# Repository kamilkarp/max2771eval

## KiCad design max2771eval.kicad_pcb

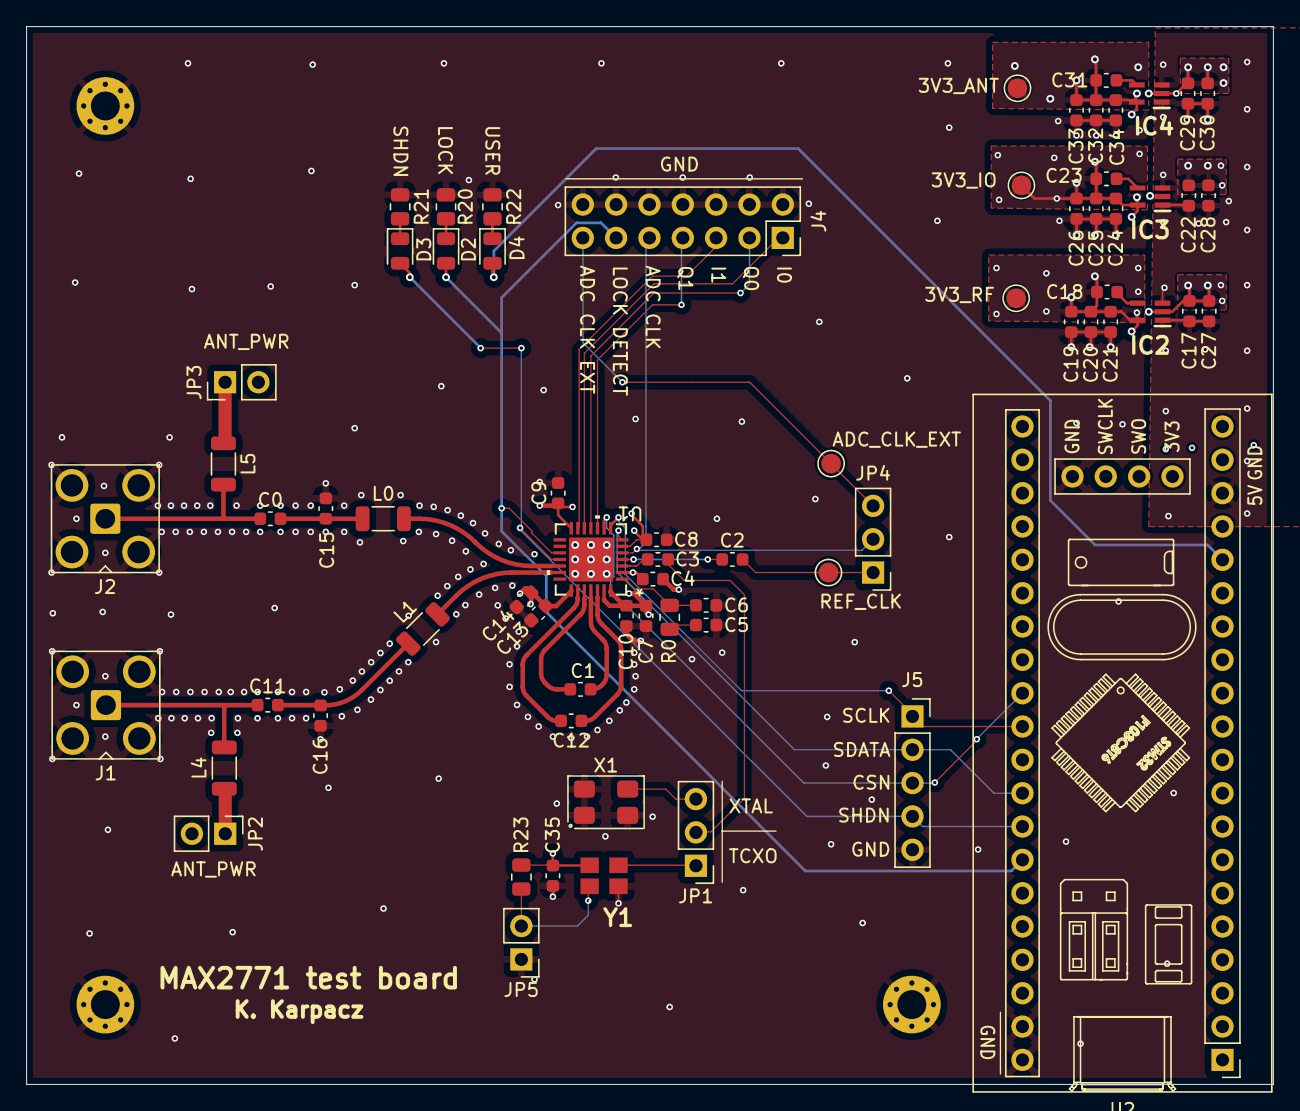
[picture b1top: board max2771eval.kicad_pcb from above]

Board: 4 copper layers, 95.0 x 80.6 mm, 72 parts (0 on the bottom side), 44 nets.

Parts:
C0, C1, C11, C12: 0.47nF; C_0603_1608Metric
C2, C3, C18, C20, C23, C25, C31, C33, C35: 10nF; C_0603_1608Metric
C4, C7, C8, C9, C10, C13, C17, C19, C22, C24, C30, C32: 0.1μF; C_0603_1608Metric
C5: 0.75nF; C_0603_1608Metric
C6: 15pF; C_0603_1608Metric
C14: 0.1nF; C_0603_1608Metric
C15: 1.7 pF; C_0603_1608Metric
C16: 1.1 pF; C_0603_1608Metric
C21, C26, C27, C28, C29, C34: 1μF; C_0603_1608Metric
D2, D3, D4: LED; D_0805_2012Metric
H1, H2, H3: MountingHole_Pad; MountingHole_2.2mm_M2_Pad_Via
IC2, IC3, IC4: MAX8510EXK33+T; SOT65P210X110-5N
J1, J2: Conn_Coaxial; SMA_Amphenol_901-143_Horizontal
J4: Conn_02x07_Odd_Even; PinSocket_2x07_P2.54mm_Vertical
J5: Conn_01x05_Socket; PinSocket_1x05_P2.54mm_Vertical
JP1, JP4: Jumper_3_Bridged12; PinHeader_1x03_P2.54mm_Vertical
JP2, JP3: Jumper_2_Bridged; PinHeader_1x02_P2.54mm_Vertical
JP5: Jumper_2_Open; PinHeader_1x02_P2.54mm_Vertical
L0: 5.6 nH; L_1206_3216Metric
L1: 8.4 nH; L_1206_3216Metric
L4, L5: 5.6nH; L_1206_3216Metric
R0: 15k; R_0805_2012Metric
R20, R21, R22: 1k; R_0805_2012Metric
R23: 25k; R_0805_2012Metric
TP1: 3V3_ANT; TestPoint_Pad_D1.5mm
TP2: 3V3_RF; TestPoint_Pad_D1.5mm
TP3: 3V3_IO; TestPoint_Pad_D1.5mm
TP4: ADC_CLK_EXT; TestPoint_Pad_D1.5mm
TP5: REF_CLK; TestPoint_Pad_D1.5mm
U1: MAX2771ETI+; 21-0140L_T2855-8_MXM
U2: YAAJ_BluePill_SWD_Breakout; YAAJ_BluePill_SWD_1
X1: 16.368MHz; Crystal_SMD_5032-4Pin_5.0x3.2mm
Y1: ATX-H11-F-24.000MHz-F25-T; ATXH11F24000MHzF25T

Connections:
+3.3V_IO: C8.1, C9.1, C23.2, C24.1, C25.1, C26.1, C35.2, IC3.5 (OUT), R23.2, TP3.1, U1.6 (VCCD), U1.14 (VCCADC), Y1.4 (VDD)
+3.3V_RF: C4.1, C7.1, C10.2, C13.2, C14.2, C18.2, C19.1, C20.1, C21.1, IC2.5 (OUT), TP2.1, U1.2 (VCCCP), U1.22 (VCCRF), U1.27 (VCCIF), U1.28 (VCCVCO)
+3.3_ANT: C31.2, C32.1, C33.1, C34.1, IC4.5 (OUT), JP2.2 (B), JP3.2 (B), TP1.1
+5V_USB: C17.2, C22.2, C27.1, C28.1, C29.1, C30.2, IC2.1 (IN), IC2.3 (~SHDN), IC3.1 (IN), IC3.3 (~SHDN), IC4.1 (IN), IC4.3 (~SHDN), U2.18 (5V)
/ADC_CLK_A: J4.9, JP4.2 (C), U1.5 (ADC_CLKIN)
/ADC_CLK_A_EXT: J4.13, JP4.3 (B), TP4.1
/A_CSN: J5.3, U1.9 (CSN), U2.29 (PA4)
/A_I0: J4.1, U1.12 (I0)
/A_I1: J4.5, U1.13 (I1)
/A_LOCK_DETECT: D2.2 (A), J4.11, U1.17 (LD), U2.34 (PB1)
/A_Q0: J4.3, U1.11 (Q0)
/A_Q1: J4.7, U1.10 (Q1)
/A_SCLK: J5.1, U1.8 (SCLK), U2.30 (PA5)
/A_SDATA: J5.2, U1.7 (SDATA), U2.32 (PA7)
/A_SHDN: D3.2 (A), J5.4, U1.18 (SHDN), U2.33 (PB0)
/REF_CLK_A: C3.2, JP1.2 (C)
/REF_CLK_OUT_A: C2.2, JP4.1 (A), TP5.1
/RF_HIGH_BAND_IN_A: C0.1, J2.1 (In), L5.2
/RF_LOW_BAND_IN_A: C11.1, J1.1 (In), L4.2
GND: C4.2, C5.2, C6.2, C7.2, C8.2, C9.2, C10.1, C13.1, C14.1, C15.1, C16.1, C17.1, C19.2, C20.2, C21.2, C22.1, C24.2, C25.2, C26.2, C27.2, C28.2, C29.2, C30.1, C32.2, C33.2, C34.2, C35.1, H1.1, H2.1, H3.1, IC2.2 (GND), IC3.2 (GND), IC4.2 (GND), J1.2 (Ext), J2.2 (Ext), J4.2, J4.4, J4.6, J4.8, J4.10, J4.12, J4.14, J5.5, JP5.1 (A), R20.1, R21.1, R22.1, U1.29 (EPAD), U2.19 (GND), U2.39 (GND), U2.40 (GND), U2.41 (GND), X1.1, X1.2, X1.4, Y1.2 (GND)
unnamed: C0.2, C15.2, L0.1
unnamed: C5.1, R0.1
unnamed: C11.2, C16.2, L1.1
unnamed: D2.1 (K), R20.2
unnamed: D3.1 (K), R21.2
unnamed: D4.2 (A), U2.16 (PB8)
unnamed: D4.1 (K), R22.2
unnamed: C18.1, IC2.4 (BP)
unnamed: C23.1, IC3.4 (BP)
unnamed: C31.1, IC4.4 (BP)
unnamed: JP1.1 (A), Y1.3 (OUTPUT)
unnamed: JP1.3 (B), X1.3
unnamed: JP2.1 (A), L4.1
unnamed: JP3.1 (A), L5.1
unnamed: JP5.2 (B), R23.1, Y1.1 (~INH)
unnamed: C2.1, U1.4 (CLKOUT)
unnamed: C6.1, R0.2, U1.1 (CPOUT)
unnamed: L0.2, U1.19 (LNAIN_HI)
unnamed: L1.2, U1.20 (LNAIN_LO)
unnamed: C1.2, U1.24 (LNAOUT_HI)
unnamed: C12.2, U1.23 (LNAOUT_LO)
unnamed: C1.1, U1.25 (MIXIN_HI)
unnamed: C12.1, U1.26 (MIXIN_LO)
unnamed: C3.1, U1.3 (XTAL)

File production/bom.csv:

Designator,Footprint,Quantity,Value,LCSC Part #
"C0, C1, C11, C12",0603,4,0.47nF,
"C10, C13, C17, C19, C22, C24, C30, C32, C4, C7, C8, C9",0603,12,0.1μF,
C14,0603,1,0.1nF,
C15,0603,1,1.7 pF,
C16,0603,1,1.1 pF,
"C18, C2, C20, C23, C25, C3, C31, C33, C35",0603,9,10nF,
"C21, C26, C27, C28, C29, C34",0603,6,1μF,
C5,0603,1,0.75nF,
C6,0603,1,15pF,
"D2, D3, D4",0805,3,LED,
"IC2, IC3, IC4",SOT65P210X110-5N,3,MAX8510EXK33+T,
"J1, J2",SMA_Amphenol_901-143_Horizontal,2,Conn_Coaxial,
J4,PinSocket_2x07_P2.54mm_Vertical,1,Conn_02x07_Odd_Even,
J5,PinSocket_1x05_P2.54mm_Vertical,1,Conn_01x05_Socket,
"JP2, JP3",PinHeader_1x02_P2.54mm_Vertical,2,Jumper_2_Bridged,
JP5,PinHeader_1x02_P2.54mm_Vertical,1,Jumper_2_Open,
L0,1206,1,5.6 nH,
L1,1206,1,8.4 nH,
"L4, L5",1206,2,5.6nH,
R0,0805,1,15k,
"R20, R21, R22",0805,3,1k,
R23,0805,1,25k,
TP1,TestPoint_Pad_D1.5mm,1,3V3_ANT,
TP2,TestPoint_Pad_D1.5mm,1,3V3_RF,
TP3,TestPoint_Pad_D1.5mm,1,3V3_IO,
TP4,TestPoint_Pad_D1.5mm,1,ADC_CLK_EXT,
TP5,TestPoint_Pad_D1.5mm,1,REF_CLK,
U1,21-0140L_T2855-8_MXM,1,MAX2771ETI+,
U2,YAAJ_BluePill_SWD_1,1,YAAJ_BluePill_SWD_Breakout,
X1,Crystal_SMD_5032-4Pin_5.0x3.2mm,1,16.368MHz,
Y1,ATXH11F24000MHzF25T,1,ATX-H11-F-24.000MHz-F25-T,

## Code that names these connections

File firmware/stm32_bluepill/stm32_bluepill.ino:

#include <Arduino.h>
#include "max2771.h"
#include "max2771_driver_bit_bang.h"

#define MAX_SHDN_PIN PB0
#define MAX_LD_PIN PB1
#define MAX_SDATA_PIN PA7
#define MAX_SCLK_PIN PA5
#define MAX_CSN_PIN PA4
#define USER_LED_PIN PB8

static Max2771DriverBitBang max2771_driver(MAX_SCLK_PIN, MAX_SDATA_PIN, MAX_CSN_PIN, MAX_LD_PIN, MAX_SHDN_PIN);
static Max2771 max2771(&max2771_driver);

void setup() {
  pinMode(USER_LED_PIN, OUTPUT);
  delay(100);
  max2771.setup();

  Serial.begin();
}

void loop() {
  String command = Serial.readStringUntil('\n');
  auto length = command.length();

  if (length <= 0) {
    return;
  }

  String substrings[5];
  size_t currentIndex = 0;
  size_t lastIndex = 0;
  size_t numberOfSubstrings = 0;


  while (currentIndex < length) {
    if ((command.charAt(currentIndex) != ':')) {
      currentIndex++;
      continue;
    }

    if (numberOfSubstrings >= 4) {
      break;
    }

    substrings[numberOfSubstrings] = command.substring(lastIndex, currentIndex);

    lastIndex = currentIndex + 1;
    numberOfSubstrings++;
    currentIndex++;
  }

  if (numberOfSubstrings < 4) {
    substrings[numberOfSubstrings] = command.substring(lastIndex);
    numberOfSubstrings++;
  }

  if (numberOfSubstrings == 2) {
    if (substrings[0] == "READ") {
      uint8_t address = substrings[1].toInt();
      auto value = max2771.readReg(address);
      Serial.println("REG:" + String(address) + ":" + String(value));
    }
  } else if (numberOfSubstrings == 3) {
    if (substrings[0] == "WRITE") {
      uint8_t address = substrings[1].toInt();
      uint32_t value = (uint32_t)(std::atoll(substrings[2].c_str()));
      max2771.writeReg(address, value);
      auto result = max2771.readReg(address);
      Serial.println("REG:" + String(address) + ":" + String(result));
    }
  }
}

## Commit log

2025-03-15 initial
2025-03-31 max2771 module
2025-03-31 finished v1
2025-04-01 outputs
2025-04-18 update bom
2025-04-18 add autosave to gitignore
2025-04-18 chore: move board to hardware folder
2025-04-18 chore: add board control app
2025-04-19 feat: bluepill firmware
2025-04-19 .gitignore
2025-04-19 chore: add vscode launch options
2025-04-19 chore: remove dart from language detaction
2025-04-20 fix: configuration for board
2025-04-21 chore: update default configuration
2025-04-21 chore: disable shutdown
2025-04-27 chore: l1 with IF filter preset
